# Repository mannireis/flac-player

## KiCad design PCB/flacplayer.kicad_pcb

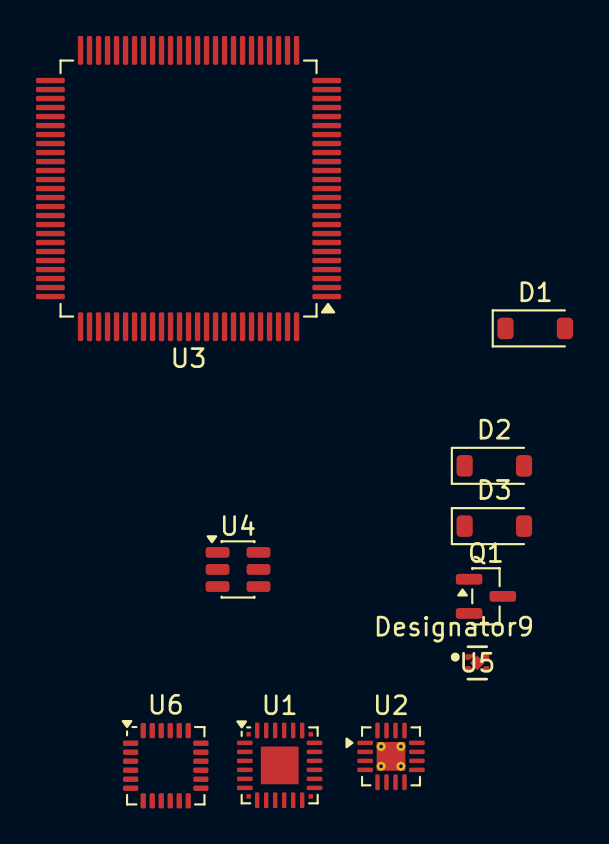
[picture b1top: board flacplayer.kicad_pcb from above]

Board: 2 copper layers, 10 parts (0 on the bottom side), 6 nets, no tracks yet.

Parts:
D1, D2, D3: MBR0530; D_SOD-123
Q1: AO3400A; SOT-23
U1: TAD5242; Texas_RGE0024R_VQFN-24-1EP_4x4mm_P0.5mm_EP2.1x2.1mm
U2: TPA6132A2RTE; WQFN-16-1EP_3x3mm_P0.5mm_EP1.6x1.6mm_ThermalVias
U3: STM32H753VITx; LQFP-100_14x14mm_P0.5mm
U4: USBLC6-2SC6; SOT-23-6
U5: TPS7A0333PDQNR; DQN0004A-MFG
U6: MPU-6050; InvenSense_QFN-24_4x4mm_P0.5mm

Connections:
+3V3: U1.6 (IOVDD), U1.23 (AVDD), U2.14 (VDD), U3.11 (VDD), U3.27 (VDD), U3.50 (VDD), U3.75 (VDD), U3.100 (VDD), U5.1 (Vout), U6.8 (VLOGIC), U6.13 (VDD)
/D+: U3.71 (PA12), U4.6 (I/O1)
/D-: U3.70 (PA11), U4.1 (I/O1)
GND: D3.1 (K), U1.4 (MD6), U1.7 (MD1), U1.8 (MD2), U1.9 (MD3), U1.10 (MD4), U1.12 (MD5), U1.13 (MD0), U1.14 (VSSA), U1.15 (VSSA), U1.16 (VSSA), U1.17 (VSSA), U1.18 (VSSA), U1.25 (VSS), U1.A1 (VSS), U1.A2 (VSS), U1.A3 (VSS), U1.A4 (VSS), U2.10 (PGND), U2.15 (SGND), U2.17 (EP), U3.10 (VSS), U3.19 (VSSA), U3.26 (VSS), U3.49 (VSS), U3.74 (VSS), U3.99 (VSS), U4.2 (GND), U5.2 (GND), U5.5 (Thermal_Pad), U6.18 (GND)
unnamed: D1.2 (A), Q1.3 (D)
unnamed: D2.1 (K), D3.2 (A)

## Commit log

2026-05-13 Researched and started making the schematic!
2026-05-17 journals and some other stuffH
2026-05-19 meow mrow :3
2026-05-25 does ts work
2026-05-26 Journal and sd cardgit add .
2026-05-29 fix component issues
2026-05-31 NEW JOURNAL WOOP WOOP
2026-05-31 oop need to work on ts more
2026-05-31 new thingies and new file
2026-05-31 clean up the repo
2026-06-12 NEW journal weeeeeeeee i talk about remaking it beh
2026-06-16 mpu6050 ayya accel and gyro + journal
2026-06-16 epaper
2026-06-16 im dum hehe
